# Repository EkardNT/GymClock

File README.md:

# GymClock

This repository contains the Arduino code, Blender models, and Kicad projects that I used to build the programmable gym clock at the [Fremont Gymnasium](https://www.fremontgymnasium.com/).

## How it works

### Hardware

The hardware components that make up the electrical part of the sign are the segments, the
digit controllers, the shared control bus, and the central controller.

- There are 70 **segments** in the display, grouped into 10 digits of 7 segments each (labeled A-G).
I designed the [segment PCB](kicad/SevenSegment/) in an elongated hexagon shape so 7 of them
could be laid together to form the shape of an 8, as is standard for 7-segment displays.
Electrically, each segment has 15V power and ground connectors at each tip of the PCB, as
well as a 3.3V connector in the middle which feeds into the base of a transistor to turn
the segment on or off. The segments contain internal resistors to limit both the 15V and
3.3V currents to the appropriate level. Having the power and ground connectors at the tip
of each segment allowed me to connect all 7 segments in a digit together end-to-end. This
reduced the number and size of wires needed per-segment. Power and ground can be connected
to only one segment and will then flow through the tip connections to the rest of the
segments in that digit.
- There are 10 **digit controllers**, one per digit. The digit controller takes input
signals from the control bus, and has 7 output wires that switch the 7 segments that
make up that display on or off (actually there is an 8th output for controlling a colon/separator
LED segment but its unused). The digit controller has no microprocessor, only fixed-function
IC components. The way that the 10 identically-constructed digit controllers are able to
know which bus signals are meant for them are by way of a 4-channel DIP switch (4 bits
giving 16 possible digit addresses - the sign uses only 10). The digit controller uses an
identity comparator IC to compare the setting of the DIP switch with 4 bits from the bus
input. Only if the 4 bits match are the remaining 3 logic lines from the bus connected to
an shift register IC on the digit controller. The shift register has 8 bits of storage,
which correspond to the 7 segments and 1 (unused) colon control outputs. The fact that a
shift register is used means that the digit controller has persistent memory - once it has
been programmed with a given 8-bit pattern, it is able to hold that pattern (aka keep the
LED segments lit) without further input needed from the central controller.
- The **central** bus is composed of 11 wires: 2 wires for 15V power and ground, 2 wires for 3.3V
power and ground, 7 wires for 3.3V logic signals. The 2 15V power and ground wires connect
directly to the tip-interconnected segments; the remaining 9 wires connect all the digit
controllers and the central controller together. All 10 digit controllers and the central
controller share the same single bus. All wires are driven high/low by the central controller
alone - there is no reverse communication from digit controller to central controller. As
described above, 4 of the logic wires carry the address bits that allow the central controller
to select a specific digit. The remaining 3 logic wires are connected to the SER, RCLK, and
SRCLK inputs of the digit controllers' shift registers. Because of my lack of experience
with bus wiring options, I used individual wires for all the bus lines, and (relatively)
enormous terminal blocks as the junction points for 3- and 4-way bus joins. Its messy, but
it works.
- The **central controller** is an ESP8266 microcontroller, embedded in a very simple
motherboard with some additional components for speaker amplification and volume control.
The ESP8266 is connected directly to the 7 bus logic lines and drives the wires high/low
to select and "program" the shift registers on the individual digits.

### Lit window

Because each digit controller has a programmable shift register, technically speaking the
display can light all 10 digits simultaneously. However, when all 7 segments are continuously
lit, a digit consumes a full 1 amp. This means having all 10 digits lit would take 10 amps,
which is way more current than I felt safe using. So instead, the display works by the
central controller iterating over each digit, turning it on, turning it off, and moving to
the next digit, in a continuous loop. The loop is so fast that our eye's persistence
of vision means that we see the entire display as being lit, even if only one digit
is lit at a time.

The above description is not fully accurate. There is a concept of a "lit window",
which is a sliding window of digits that are all lit at once. The above descripton was of
a lit window of length 1, but the display actually uses a lit window of size 3. There is
still a loop, but it works by turning on the next digit, then turning off the digit 3 spaces
back. At any point in time, 3 digits are lit. The size of the lit window is a tradeoff
between brightness and current consumption. The longer the lit window, the more time that
digits spend lit up and so the brighter they look. However, the longer the lit window, the
more amps that are used by the display. A lit window of size N should use N amps. I found
that a lit window of 3 gave good brightness results while still keeping the current consumption
reasonable.

Speaking of current consumption, current measurements using my bench power supply as well
as a Kill-A-Watt device show significantly lower current usage than the ~3 amps I would
expect for a fully-lit display (all digits showing 8s). I'm not sure whether this is simply
measurement error (power switching on and off too fast for accurate measurements) or whether
the LEDs have some sort of "warmup time" where they don't immediately get to full current draw
until some time after being turned on. Either way, I used a 4-amp power supply to be safe.

**Historical note**: The shift register-based digit controller is actually the second
version of digit controller. The first version used a 3-to-8 demultiplexer and had no memory.
All 7 wires on the bus were effectively address bits for the 70 segments on the board, and
the central controller could turn on exactly 1 segment at a time. This resulted in
fantastically low current consumption, but the display was too dim. I had to replace and
rewire the 10 digit controllers with the second generation shift register-based one,
resulting in higher current draw but also much more satisfactory brightness.

### Software

I used the [ESP8266 Arduino core](https://github.com/esp8266/Arduino) to program the
central controller. The various HTTP services - the user control pages, the admin pages,
the remote update server - were all built using code from the ESP8266 Arduino core library.
The reason they all are so basic is because I had to store all the HTML pages as string
literals - no fancy web frameworks or templating engines here!

To implement the display functions (clock, stopwatch, etc) I used the
[AceRoutine](https://github.com/bxparks/AceRoutine) library to write them as coroutines instead
of manually implemented state machines. Although I found a
[bug](https://github.com/bxparks/AceRoutine/issues/19) in the library, it was overall an
enormous help and made it possible to implement much more elaborate functions than I would
have had the patience to do otherwise (and much quicker too!).

## How to update

If you're ok with pulling the sign down, you can flash the esp8266 via the usb port as normal. The sketch also supports wireless flashing of signed binaries. The public key for the signing is the [public.key](public.key) file in this repo. The private key is on my laptop. I'll also store a copy of the private key in a USB drive and put the drive inside the sign itself.

## How to debug

I created a [Debug](debug.h) class as a wrapper around the Serial class which has the ability
to redirect debug print statements via UDP packets to some UDP address on the network. This
means that you can view Serial/debug statements without needing to be plugged in to the ESP8266's
USB port! I also created the [udp_listener](https://github.com/EkardNT/udp_listener) utility
program as an easy way of viewing the broadcast UDP debug info on your terminal.

UDP debug redirection is disabled by default. It can be toggled on or off from the user or admin
index pages.

## Errata

I had a bug in the DigitController2 schematic that I didn't catch until after I had the PCBs manufactured. The bug was that the SER and SRCLK lines are swapped. I fixed the bug in the schematic, but did not order new PCBs because I was able to work around the bug by simply swapping the SER and SRCLK wiring lines from the central controller to the main bus.

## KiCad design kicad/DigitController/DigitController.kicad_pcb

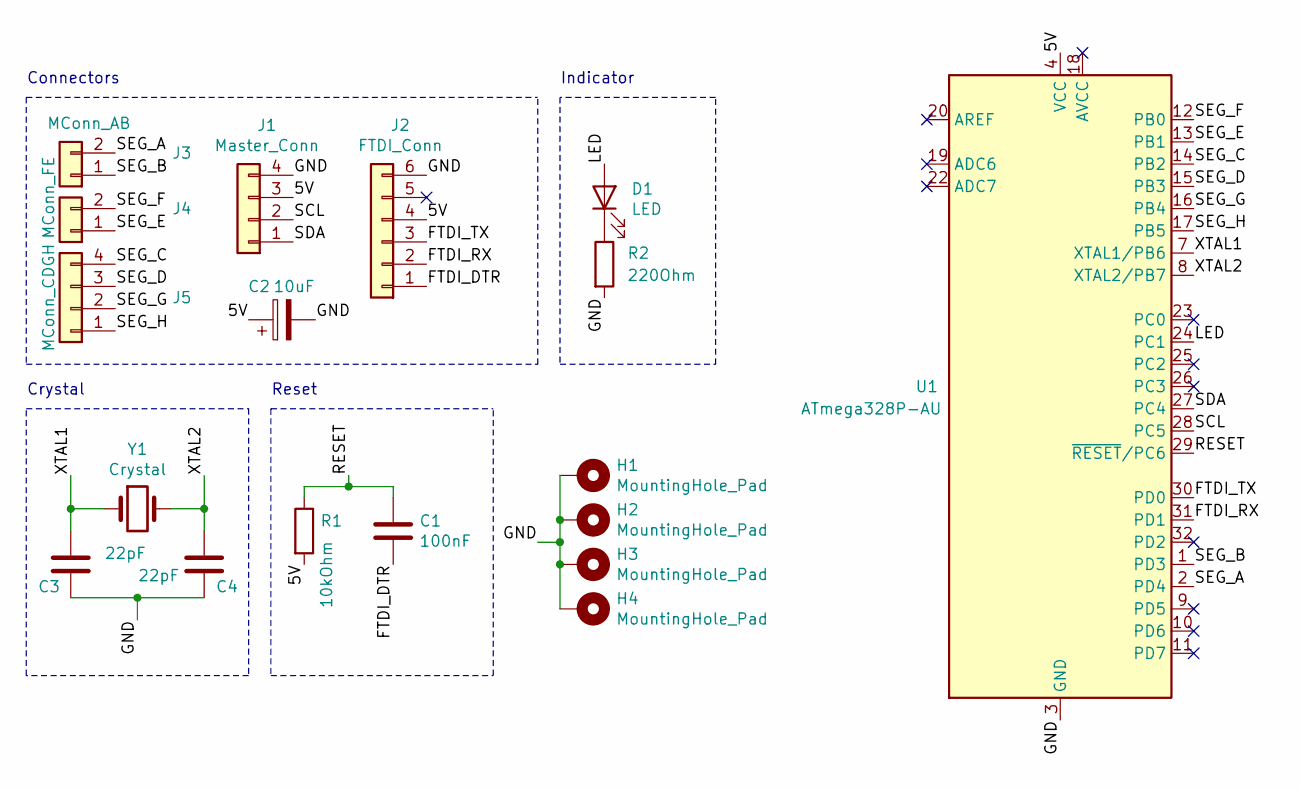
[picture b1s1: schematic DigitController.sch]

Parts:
C1: 100nF; C_1206_3216Metric_Pad1.42x1.75mm_HandSolder
C2: 10uF; C_1206_3216Metric_Pad1.42x1.75mm_HandSolder
C3, C4: 22pF; C_1206_3216Metric_Pad1.42x1.75mm_HandSolder
D1: LED; Kingbright_AM2520SURCK03
H1, H2, H3, H4: MountingHole_Pad; MountingHole_2.5mm_Pad_Via
J1: Master_Conn; PinHeader_1x04_P2.54mm_Vertical
J2: FTDI_Conn; PinHeader_1x06_P2.54mm_Vertical
J3: MConn_AB; PinHeader_1x02_P2.54mm_Vertical
J4: MConn_FE; PinHeader_1x02_P2.54mm_Vertical
J5: MConn_CDGH; PinHeader_1x04_P2.54mm_Vertical
R1: 10kOhm; R_1206_3216Metric_Pad1.42x1.75mm_HandSolder
R2: 220Ohm; R_1206_3216Metric_Pad1.42x1.75mm_HandSolder
U1: ATmega328P-AU; TQFP-32_7x7mm_P0.8mm
Y1: Crystal; Resonator-2Pin_W10.0mm_H5.0mm

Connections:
/5V: C2.1, J1.3, J2.4, R1.2, U1.4 (VCC), U1.6 (VCC)
/FTDI_DTR: C1.2, J2.1
/FTDI_RX: J2.2, U1.31 (PD1)
/FTDI_TX: J2.3, U1.30 (PD0)
/GND: C2.2, C3.2, C4.2, H1.1, H2.1, H3.1, H4.1, J1.4, J2.6, R2.2, U1.3 (GND), U1.5 (GND), U1.21 (GND)
/LED: D1.2 (A), U1.24 (PC1)
/RESET: C1.1, R1.1, U1.29 (~RESET~/PC6)
/SCL: J1.2, U1.28 (PC5)
/SDA: J1.1, U1.27 (PC4)
/SEG_A: J3.2, U1.2 (PD4)
/SEG_B: J3.1, U1.1 (PD3)
/SEG_C: J5.4, U1.14 (PB2)
/SEG_D: J5.3, U1.15 (PB3)
/SEG_E: J4.1, U1.13 (PB1)
/SEG_F: J4.2, U1.12 (PB0)
/SEG_G: J5.2, U1.16 (PB4)
/SEG_H: J5.1, U1.17 (PB5)
/XTAL1: C3.1, U1.7 (XTAL1/PB6), Y1.1
/XTAL2: C4.1, U1.8 (XTAL2/PB7), Y1.2
unnamed: D1.1 (K), R2.1

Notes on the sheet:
Crystal
Reset
Connectors
Indicator

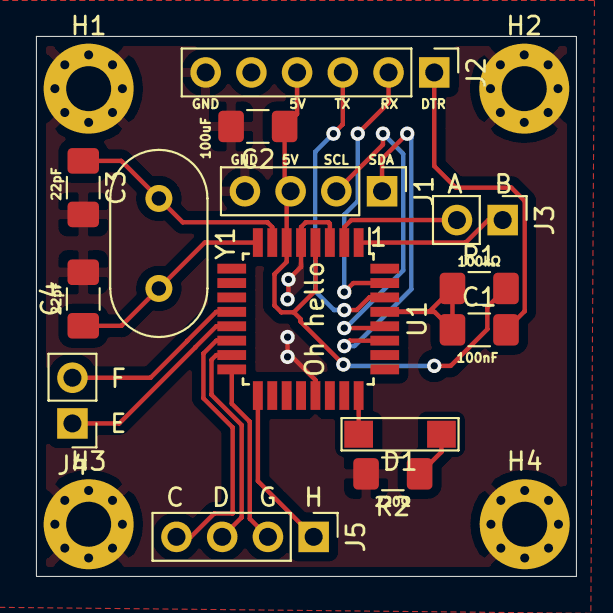
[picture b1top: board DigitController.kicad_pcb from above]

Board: 2 copper layers, 30.0 x 30.0 mm, 18 parts (0 on the bottom side), 20 nets.

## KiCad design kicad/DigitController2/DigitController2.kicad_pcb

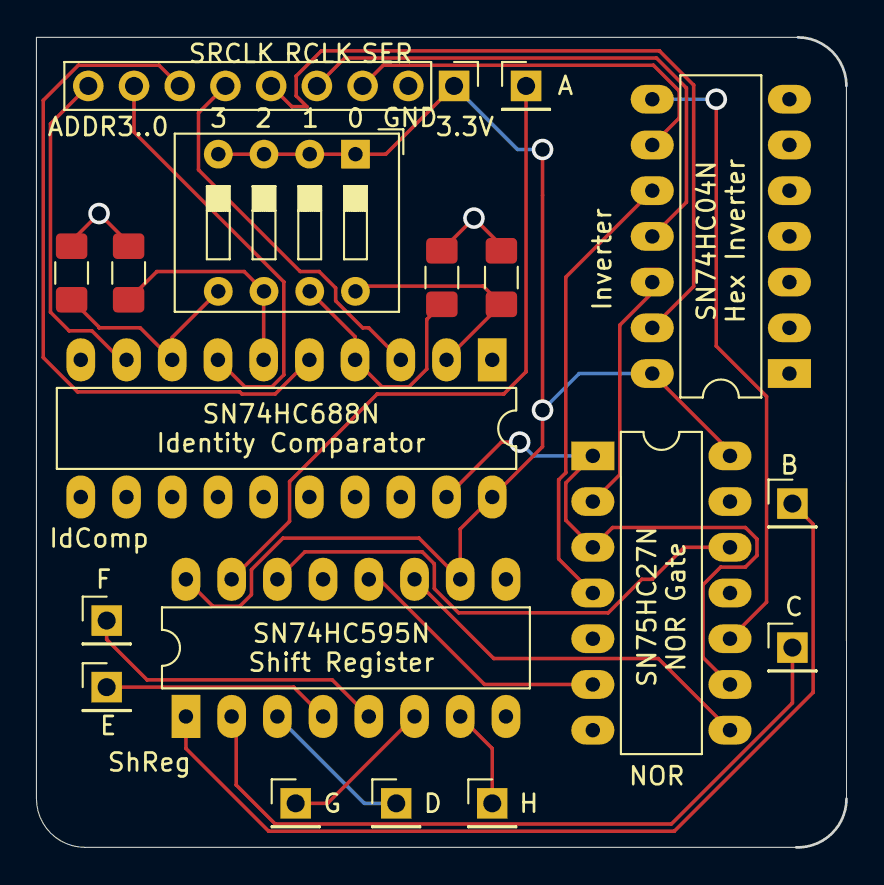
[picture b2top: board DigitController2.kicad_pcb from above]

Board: 2 copper layers, 45.0 x 45.0 mm, 18 parts (0 on the bottom side), 28 nets.

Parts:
IC1: SN74HC27N - NOR; DIP-14_W7.62mm_LongPads
J1: Conn_SegH; PinHeader_1x01_P2.54mm_Vertical
J2: Conn_SegG; PinHeader_1x01_P2.54mm_Vertical
J3: Conn_SegF; PinHeader_1x01_P2.54mm_Vertical
J4: Conn_Inputs; PinHeader_1x09_P2.54mm_Vertical
J5: Conn_SegE; PinHeader_1x01_P2.54mm_Vertical
J6: Conn_SegD; PinHeader_1x01_P2.54mm_Vertical
J7: Conn_SegC; PinHeader_1x01_P2.54mm_Vertical
J8: Conn_SegB; PinHeader_1x01_P2.54mm_Vertical
J9: Conn_SegA; PinHeader_1x01_P2.54mm_Vertical
R1, R2, R3, R4: 47k; R_1206_3216Metric_Pad1.42x1.75mm_HandSolder
SW1: SW_DIP_x04; SW_DIP_SPSTx04_Slide_9.78x12.34mm_W7.62mm_P2.54mm
U1: SN74HC04N - INVERTER; DIP-14_W7.62mm_LongPads
U2: 74HC688 - IDENTITY COMPARATOR; DIP-20_W7.62mm_LongPads
U3: 74HC595 - Shift Register; DIP-16_W7.62mm_LongPads

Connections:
/ADDR0_IN: J4.6, U2.3
/ADDR1_IN: J4.7, U2.5
/ADDR2_IN: J4.8, U2.7
/ADDR3_IN: J4.9, U2.9
/DIGIT_SELECT: IC1.1, IC1.3, IC1.9, U2.19
/GND: IC1.5, IC1.7, IC1.11, IC1.13, J4.2, R1.2, R2.2, R3.2, R4.2, U1.1, U1.2, U1.3, U1.4, U1.5, U1.6, U1.7, U2.1, U2.10, U2.11, U2.12, U2.13, U2.14, U2.15, U2.16, U2.17, U2.18, U3.8, U3.13
/RCLK_IN: J4.4, U1.11
/SEG_A: J9.1, U3.15
/SEG_B: J8.1, U3.1
/SEG_C: J7.1, U3.2
/SEG_D: J6.1, U3.3
/SEG_E: J5.1, U3.4
/SEG_F: J3.1, U3.5
/SEG_G: J2.1, U3.6
/SEG_H: J1.1, U3.7
/SER_IN: J4.3, U1.9
/SRCLK_IN: J4.5, U1.13
/VCC: IC1.14, J4.1, SW1.1, SW1.2, SW1.3, SW1.4, U1.14, U2.20, U3.10, U3.16
unnamed: IC1.2, U1.12
unnamed: IC1.4, U1.10
unnamed: IC1.6, U3.12
unnamed: IC1.8, U3.11
unnamed: IC1.10, U1.8
unnamed: IC1.12, U3.14
unnamed: R1.1, SW1.5, U2.8
unnamed: R2.1, SW1.6, U2.6
unnamed: R3.1, SW1.7, U2.4
unnamed: R4.1, SW1.8, U2.2

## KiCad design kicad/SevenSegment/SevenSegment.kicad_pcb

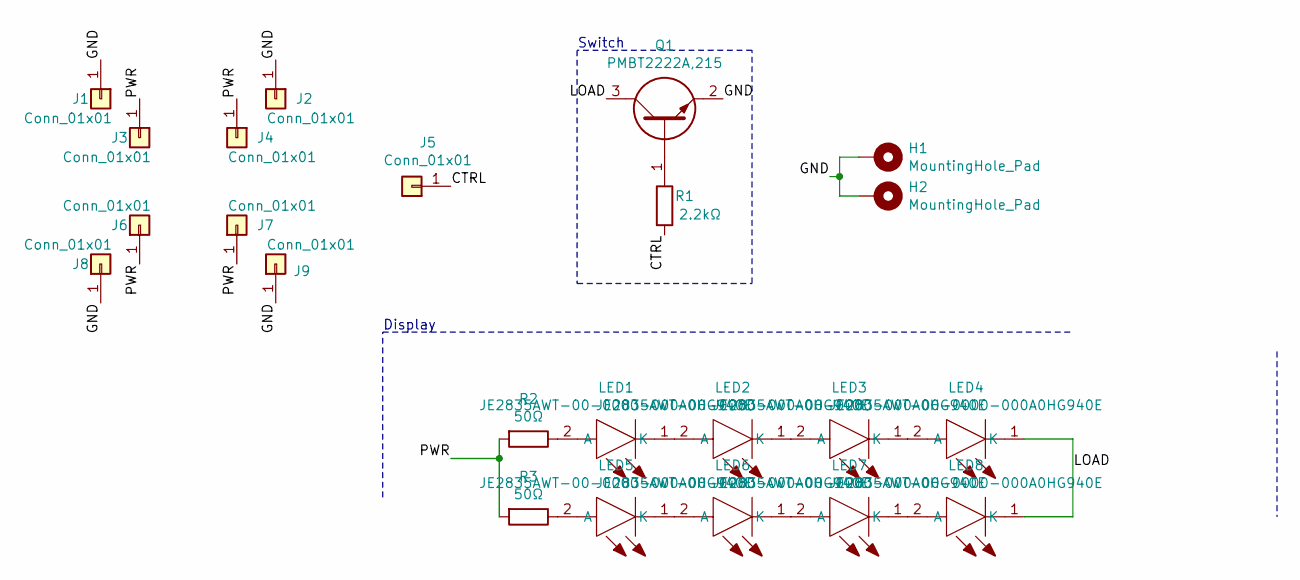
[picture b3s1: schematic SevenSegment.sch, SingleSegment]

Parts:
H1, H2: MountingHole_Pad; MountingHole_4mm_Pad_Via
J1, J2, J3, J4, J5, J6, J7, J8, J9: Conn_01x01; Pin_D1.0mm_L10.0mm
LED1, LED2, LED3, LED4, LED5, LED6, LED7, LED8: JE2835AWT-00-0000-000A0HG940E; JK2835AWT000000000B0HL430E; Manufacturer_Part_Number JE2835AWT-00-0000-000A0HG940E; Mouser Part Number 941-JE2835W00A0HG940
Q1: PMBT2222A,215; SOT-23_HandSoldering; Mouser Part Number 771-PMBT2222A-T/R
R1: 2.2kΩ; R_1206_3216Metric_Pad1.42x1.75mm_HandSolder
R2, R3: 50Ω; R_1206_3216Metric_Pad1.42x1.75mm_HandSolder

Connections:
/CTRL: J5.1, R1.2
/GND: H1.1, H2.1, J1.1, J2.1, J8.1, J9.1, Q1.2
/LOAD: LED4.1 (K), LED8.1 (K), Q1.3
/PWR: J3.1, J4.1, J6.1, J7.1, R2.2, R3.2
unnamed: LED1.1 (K), LED2.2 (A)
unnamed: LED1.2 (A), R2.1
unnamed: LED2.1 (K), LED3.2 (A)
unnamed: LED3.1 (K), LED4.2 (A)
unnamed: LED5.1 (K), LED6.2 (A)
unnamed: LED5.2 (A), R3.1
unnamed: LED6.1 (K), LED7.2 (A)
unnamed: LED7.1 (K), LED8.2 (A)
unnamed: Q1.1, R1.1

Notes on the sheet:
Switch
Display

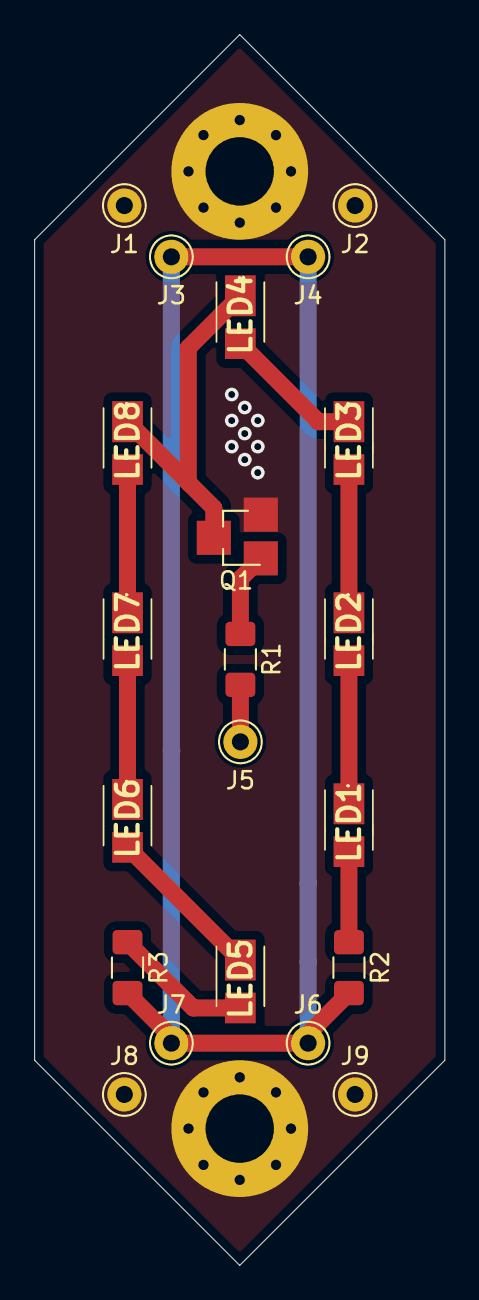
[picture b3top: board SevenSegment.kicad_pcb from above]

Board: 2 copper layers, 24.0 x 72.0 mm, 23 parts (0 on the bottom side), 13 nets.

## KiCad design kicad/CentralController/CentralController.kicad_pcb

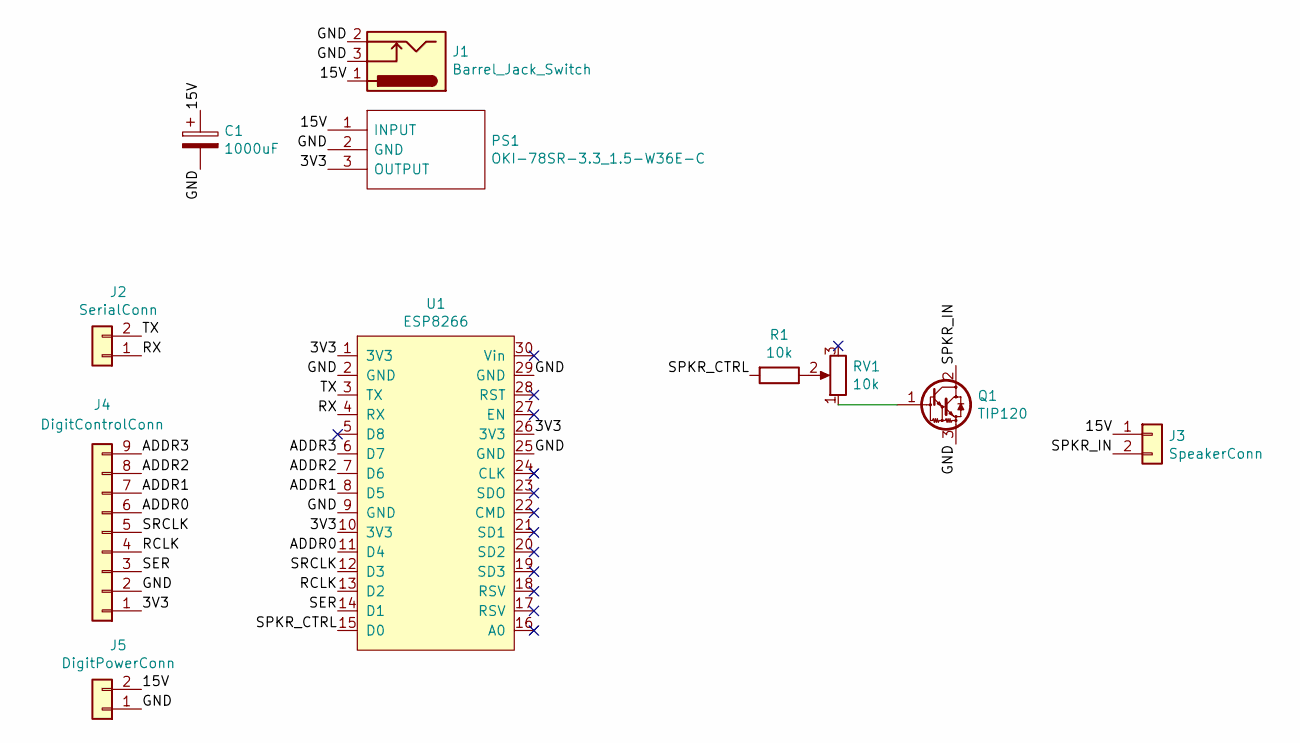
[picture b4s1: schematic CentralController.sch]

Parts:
C1: 1000uF; CP_Radial_D10.0mm_P5.00mm
J1: Barrel_Jack_Switch; BarrelJack_Horizontal
J2: SerialConn; PinHeader_1x02_P2.54mm_Vertical
J3: SpeakerConn; PinHeader_1x02_P2.54mm_Vertical
J4: DigitControlConn; PinHeader_1x09_P2.54mm_Vertical
J5: DigitPowerConn; PinHeader_1x02_P2.54mm_Vertical
PS1: OKI-78SR-3.3_1.5-W36E-C; OKI-78SR_V; Mouser Part Number 580-78SR3.3/1.5W36EC
Q1: TIP120; TO-220-3_Vertical
R1: 10k; R_Axial_DIN0207_L6.3mm_D2.5mm_P10.16mm_Horizontal
RV1: 10k; Potentiometer_Piher_T-16H_Single_Horizontal
U1: ESP8266; ESP8266NodeMCU

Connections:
/3V3: J4.1, PS1.3 (OUTPUT), U1.1 (3V3), U1.10 (3V3), U1.26 (3V3)
/15V: C1.1, J1.1, J3.1, J5.2, PS1.1 (INPUT)
/ADDR0: J4.6, U1.11 (D4)
/ADDR1: J4.7, U1.8 (D5)
/ADDR2: J4.8, U1.7 (D6)
/ADDR3: J4.9, U1.6 (D7)
/GND: C1.2, J1.2, J1.3, J4.2, J5.1, PS1.2 (GND), Q1.3 (E), U1.2 (GND), U1.9 (GND), U1.25 (GND), U1.29 (GND)
/RCLK: J4.4, U1.13 (D2)
/RX: J2.1, U1.4 (RX)
/SER: J4.3, U1.14 (D1)
/SPKR_CTRL: R1.2, U1.15 (D0)
/SPKR_IN: J3.2, Q1.2 (C)
/SRCLK: J4.5, U1.12 (D3)
/TX: J2.2, U1.3 (TX)
unnamed: Q1.1 (B), RV1.1
unnamed: R1.1, RV1.2

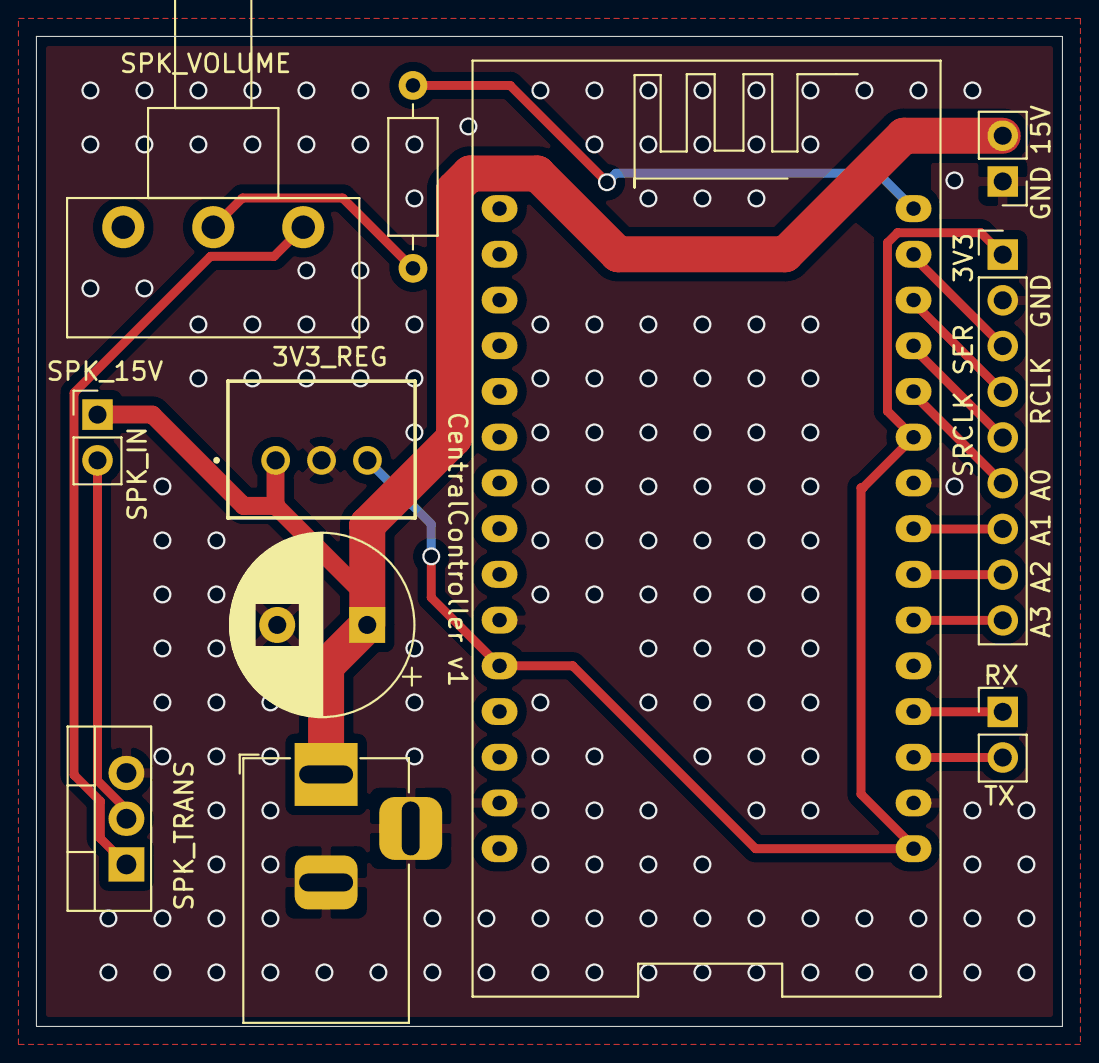
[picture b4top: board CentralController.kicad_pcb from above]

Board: 2 copper layers, 57.0 x 55.0 mm, 11 parts (0 on the bottom side), 16 nets.

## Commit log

2020-10-26 Initial commit.
2020-11-07 Copy over files from desktop into git.
2020-11-07 Remove my commented out home wifi details.
2020-11-07 Add public.key for signing.
2020-11-07 Update readme.
2020-11-07 Add errata note about the SER/SRCLK bug.
2020-11-07 Add image of inside
2020-11-07 Show image in readme.
2020-11-07 Start to use coroutines for programs.
2020-11-07 Add countdown program, remove loop function.
2020-11-07 Implement stopwatch.
2020-11-07 Add beep interval feature to stopwatch, although sound not yet implemented.
2020-11-07 Some rearrangement and cleanup.
2020-11-08 Remove colon support from updateDigit. Never happening.
2020-11-08 Small fixes.
2020-11-08 Started sound implementation. Not working yet.
2020-11-08 Added 'how it works' section to readme.
2020-11-08 Minor readme update.
2020-11-08 Change some string literals to progmem.
2020-11-09 Got sound working.
2020-11-09 Update countdown behavior, add some sounds.
2020-11-09 Remove old comments.
2020-11-09 Remove unnecessary Hours input for Stopwatch and Countdown.
2020-11-09 Update countdown slightly.
2020-11-09 Minor comment change.
2020-11-09 Improve countdown program activation page.
2020-11-09 Show RSSI for connected network in admin screen.
2020-11-09 Add wifi info to user index page.
2020-11-09 Add reboot button to user index.
2020-11-09 Enable auto reconnect.
2020-11-11 Remove default values from some fields.
2020-11-11 Create a Debug wrapper around serial that will eventually enable me to also send data to a UDP destination.
2020-11-11 Add missing placeholder.
2020-11-11 Fix typo.
2020-11-11 Improve stopwatch function page.
2020-11-12 Start working on scored countdown program.
2020-11-12 Fill out scored countdown coroutine.
2020-11-12 Add links for incrementing and decrementing the two scores for scored countdown.
2020-11-12 Added debug dump command.
2020-11-12 Add sound routine status to debug dump.
2020-11-13 Added shared CSS stylesheet.
2020-11-13 Replace /home/drake with /home/drake in build.sh.
2020-11-13 Extract admin_ui.h.
2020-11-13 Extracted user_ui.h
2020-11-13 Moved stylesheet into shared_ui.h.
2020-11-14 Fix UDB -> UDP typo.
2020-11-14 Misc.
2020-11-15 Add debug statements to user and admin UI endpoints and fix indentation.
2020-11-16 Treat empty string form argument as a not-present value.
2020-11-24 Disable Nagle's algorithm for admin and user servers.
2020-12-20 Remove nodelay settings.
2020-12-20 Extracted EEPROM-handling code to separate settings file, making it easier to add more settings.
2020-12-21 Implement static IP configuration.
2020-12-21 Reenable network auto-restart, instead of requiring a manual device reset.
2021-09-08 Start work on ESP32 version.
2021-09-08 Implement reboot admin screen.
2021-09-08 Enable admin UDP debug enable/disable screens.
2021-09-10 Start to add station mode wifi support back in.
2021-09-10 Pull time from NTP.
2021-09-10 Extract ntp functions.
2021-09-10 Get NTP working.
2021-09-11 Add display for STA WiFi info to admin index page, and add AceRoutine library.
2021-09-27 WIP checkpoint
